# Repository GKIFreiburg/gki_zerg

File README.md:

# gki_zerg
Description- and bringup-packages for the Zerg robot at Grundlagen der KI, University of Freiburg

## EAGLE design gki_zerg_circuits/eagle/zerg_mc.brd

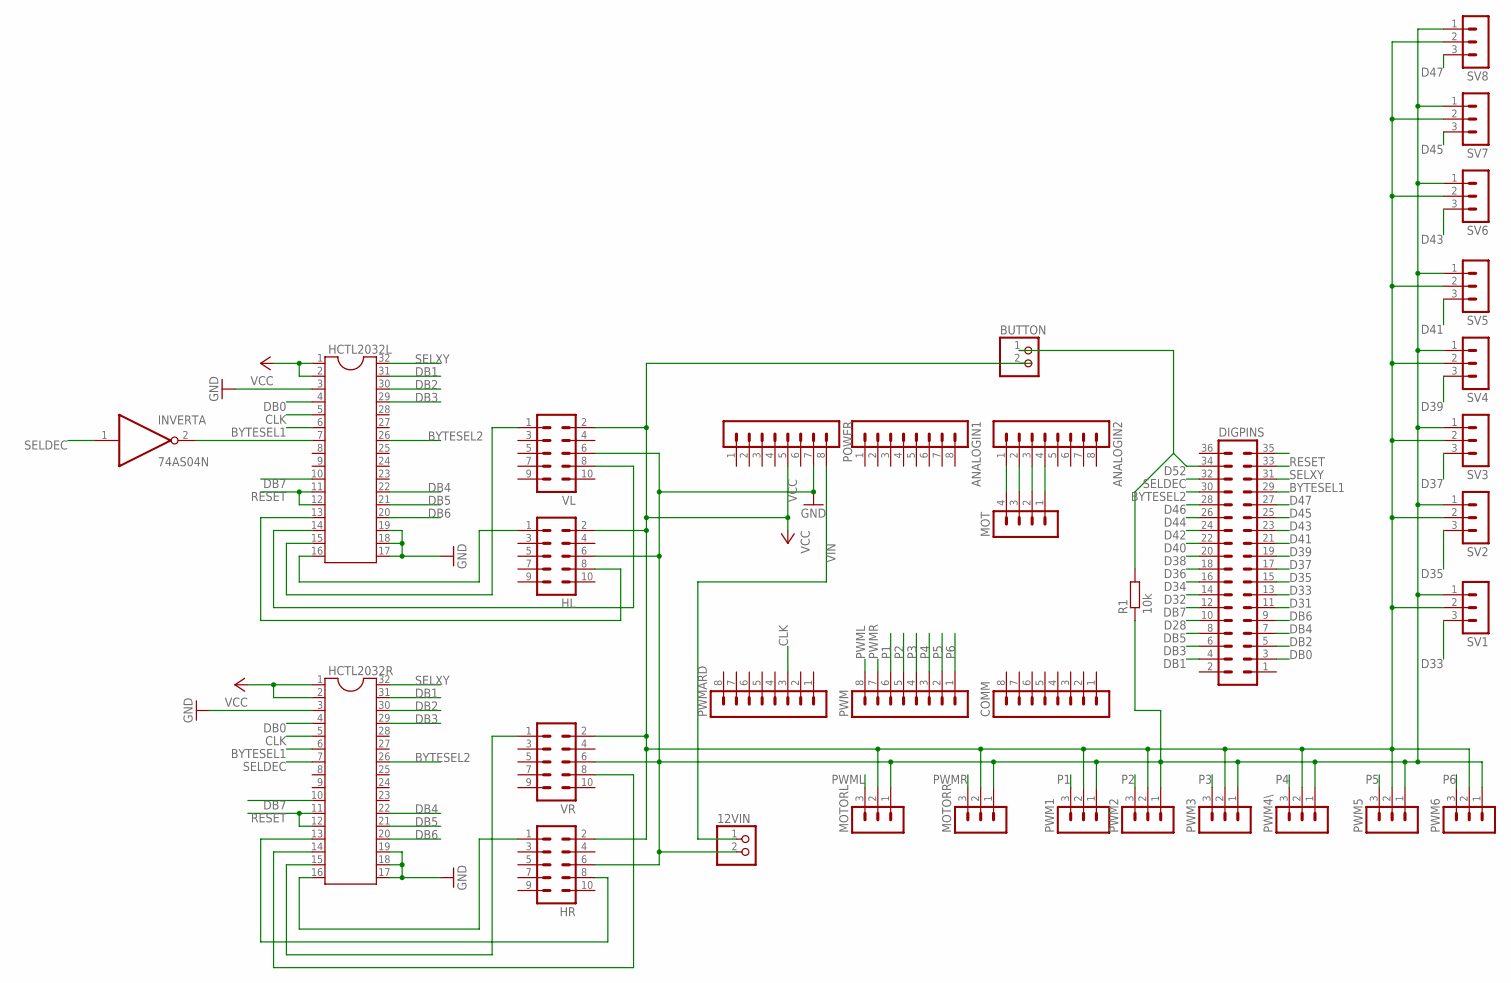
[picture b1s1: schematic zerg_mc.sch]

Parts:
12VIN: PINHD-1X2; 1X02
ANALOGIN1, ANALOGIN2: MA08-1
BUTTON: PINHD-1X2; 1X02
COMM: MA08-1
DIGPINS: MA18-2
HCTL2032L, HCTL2032R: DIL32
HL: MA05-2
HR: MA05-2
INVERT: 74AS04N; DIL14
MOT: MA04-1
MOTORL: MA03-1
MOTORR: MA03-1
POWER: MA08-1
PWM: MA08-1
PWM1, PWM2, PWM3, PWM4\, PWM5, PWM6: MA03-1
PWMARD: MA08-1
R1: 10k; 0207/10
SV1, SV2, SV3, SV4, SV5, SV6, SV7, SV8: MA03-1
VL: MA05-2
VR: MA05-2

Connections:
BYTESEL1: DIGPINS.29, HCTL2032L.6, HCTL2032R.6
BYTESEL2: DIGPINS.30, HCTL2032L.26, HCTL2032R.26
CLK: HCTL2032L.5, HCTL2032R.5, PWMARD.3
D28: DIGPINS.10
D31: DIGPINS.11
D32: DIGPINS.14
D33: DIGPINS.13, SV1.3
D34: DIGPINS.16
D35: DIGPINS.15, SV2.3
D36: DIGPINS.18
D37: DIGPINS.17, SV3.3
D38: DIGPINS.20
D39: DIGPINS.19, SV4.3
D40: DIGPINS.22
D41: DIGPINS.21, SV5.3
D42: DIGPINS.24
D43: DIGPINS.23, SV6.3
D44: DIGPINS.26
D45: DIGPINS.25, SV7.3
D46: DIGPINS.28
D47: DIGPINS.27, SV8.3
D52: BUTTON.1, DIGPINS.34, R1.2
DB0: DIGPINS.3, HCTL2032L.4, HCTL2032R.4
DB1: DIGPINS.4, HCTL2032L.31, HCTL2032R.31
DB2: DIGPINS.5, HCTL2032L.30, HCTL2032R.30
DB3: DIGPINS.6, HCTL2032L.29, HCTL2032R.29
DB4: DIGPINS.7, HCTL2032L.22, HCTL2032R.22
DB5: DIGPINS.8, HCTL2032L.21, HCTL2032R.21
DB6: DIGPINS.9, HCTL2032L.20, HCTL2032R.20
DB7: DIGPINS.12, HCTL2032L.10, HCTL2032R.10
GND: 12VIN.2, HCTL2032L.3, HCTL2032L.17, HCTL2032L.18, HCTL2032L.19, HCTL2032R.3, HCTL2032R.17, HCTL2032R.18, HCTL2032R.19, HL.6, HR.6, INVERT.7 (GND), MOTORL.1, MOTORR.1, POWER.7, PWM1.1, PWM2.1, PWM3.1, PWM4\.1, PWM5.1, PWM6.1, R1.1, SV1.1, SV2.1, SV3.1, SV4.1, SV5.1, SV6.1, SV7.1, SV8.1, VL.6, VR.6
HLA: HCTL2032L.16, HL.1
HLB: HCTL2032L.13, HL.8
HRA: HCTL2032R.16, HR.1
HRB: HCTL2032R.13, HR.8
unnamed: ANALOGIN2.1, MOT.4
unnamed: HCTL2032L.7, INVERT.2 (O)
unnamed: ANALOGIN2.2, MOT.3
unnamed: ANALOGIN2.3, MOT.2
unnamed: ANALOGIN2.4, MOT.1
P1: PWM.6, PWM1.3
P2: PWM.5, PWM2.3
P3: PWM.4, PWM3.3
P4: PWM.3, PWM4\.3
P5: PWM.2, PWM5.3
P6: PWM.1, PWM6.3
PWML: MOTORL.3, PWM.8
PWMR: MOTORR.3, PWM.7
RESET: DIGPINS.33, HCTL2032L.11, HCTL2032L.12, HCTL2032R.11, HCTL2032R.12
SELDEC: DIGPINS.32, HCTL2032R.7, INVERT.1 (I)
SELXY: DIGPINS.31, HCTL2032L.32, HCTL2032R.32
VCC: HCTL2032L.1, HCTL2032L.2, HCTL2032R.1, HCTL2032R.2, HL.2, HR.2, INVERT.14 (VCC), MOTORL.2, MOTORR.2, POWER.5, PWM1.2, PWM2.2, PWM3.2, PWM4\.2, PWM5.2, PWM6.2, SV1.2, SV2.2, SV3.2, SV4.2, SV5.2, SV6.2, SV7.2, SV8.2, VL.2, VR.2
VIN: 12VIN.1, POWER.8
VLA: HCTL2032L.15, VL.1
VLB: HCTL2032L.14, VL.8
VRA: HCTL2032R.15, VR.1
VRB: HCTL2032R.14, VR.8

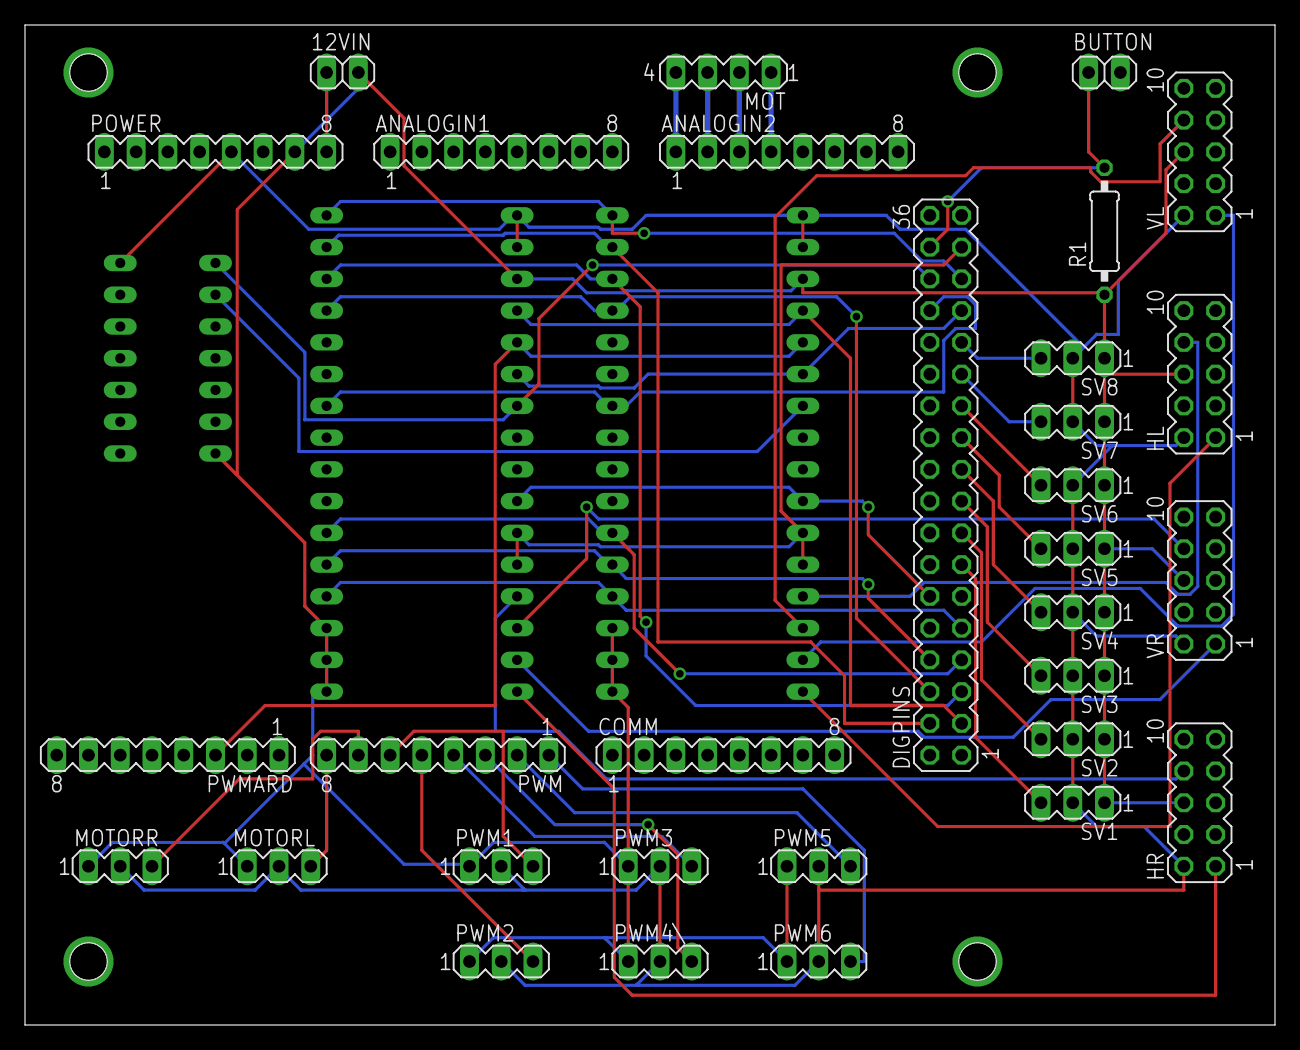
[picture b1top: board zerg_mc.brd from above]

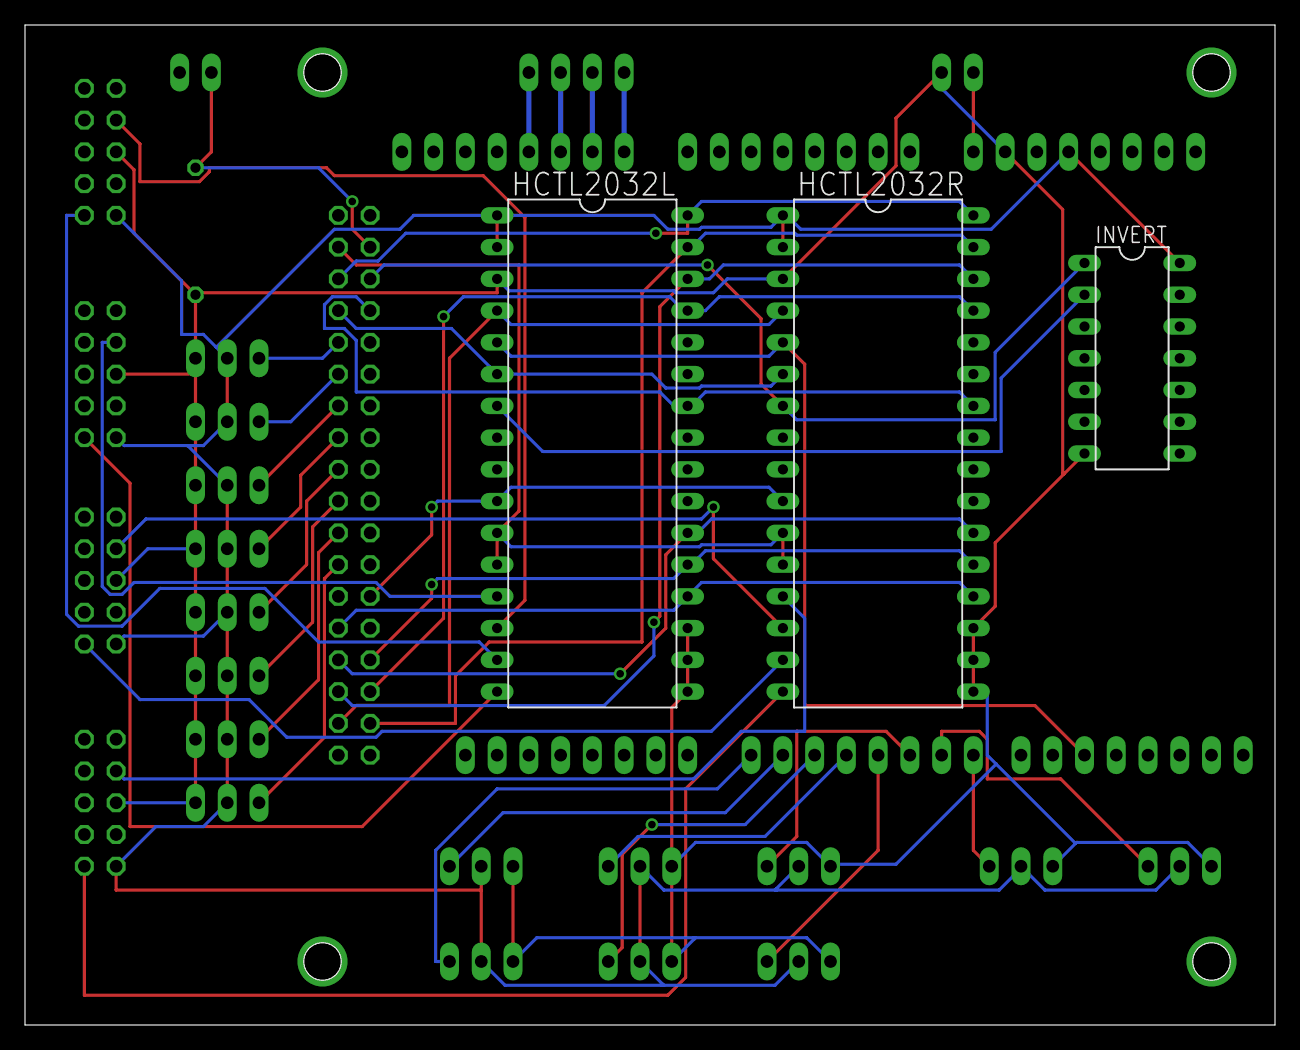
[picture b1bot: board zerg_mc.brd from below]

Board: 2 copper layers, 100.0 x 80.0 mm, 34 parts (3 on the bottom side), 47 nets.

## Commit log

2016-09-13 upgraded robot description from hydro, cleanup of urdf
2016-09-28 added gripper to urdf
2016-09-29 moved modeled gki_zerg_bringup after gki_turtlebot_bringup
2016-09-29 added arduino program for zerg motor controller
2016-09-29 added launch files for gki_zerg
2016-09-29 added gripper launch files, bugfixes in motor controller
2016-09-29 fixed topics in launch files
2016-09-29 added launch file for gripper
2016-09-29 replaced gki_turtlebot_teleop with gki_teleop
2016-09-29 improved zerg urdf, corrected topics in launch files
2016-09-30 fixed topic names
2016-10-04 corrected param names for zerg odometry
2016-10-04 removed robot pose ekf
2016-10-04 changed to dynamic cycletime
2016-10-04 added move_base configuration for zerg robot
2016-10-05 parameter tuning and bugfixes in launch files
2016-10-06 finished infrasensor and tuned pid
2016-10-06 parameter tuning
2016-10-07 added tf buffer server
2016-10-07 increased servo velocities
2016-11-22 added eagle files
